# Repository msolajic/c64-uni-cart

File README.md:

# c64-uni-cart
Hardware design of Magic Desk and Ocean compatible cartridge for the Commodore 64

This is the hardware part that accompanies the project of [Magic Desk Cartridge Generator](https://bitbucket.org/zzarko/magic-desk-cartridge-generator/)

This project is free to use and you can use any PCB manufacturer by downloading the Gerber files, but if you would like to support my work and help with further C64 hardware development you can order these PCBs on PCBWay trough this link:

You will get cheap and professionally made PCBs, I will get credits that will help with this and [other projects](https://www.pcbway.com/project/member/?bmbno=1DE407A1-1650-47). Also, if you have to register to that site, [you can use this link](https://pcbway.com/g/YFnBAc) to get bonus initial credit.

Hardware Description
--------------------

Magic Desk cartridges, in their original form, could hold up to 128Kb of code, or up to 16 banks of 8Kb each. Bank selection is done by writing a byte to $DE00. If bit 8 is set, then EXROM is disabled and RAM in the range of $8000 - $9FFF is usable.

This cartridge expands on the idea by having 128 banks of 8Kb available, thus the maximum size is 1 Mb.

Inputs of an 8-bit latch (74LS273) are connected to the data lines. Correct decoding for the I/O1 signal is done by combining PHI2 and I/O1 trough the NOR gates of 74LS02. The only feature that is deviant from the original Magic Desk specification, is that when you disable the cartridge by writing a value of $80 or larger to $DE00, the banking mechanism gets locked and no more write attempts to $DE00 will change the register's state until a hardware reset is performed. This had to be done because some programs would unintentionally write to $DE00 (or any other location in the I/O1 range) and sometimes, if $01 is wrongly set by the program, it could result in a crash. Since the use of this particular cartrige is primarily to enable making onefile program compilations trough the [Magic Desk Cartridge Generator](https://bitbucket.org/zzarko/magic-desk-cartridge-generator/), we have decided to do it this way. If you want (or need) full compatibility with the original Magic Desk cartridge hardware, we have left a jumper to disable this behaviour. Cut the track exposed on the LOCK jumper ("YES" position) on the bottom side of the cartridge PCB, and connect it to the "NO" position. This way the locking mechanism is disabled, but still you can remove the cartridge from the memory map by setting the bit 7 of the latch high.

The PCB was designed to accomodate various types of EPROMs and their FLASH variants. The smallest EPROM you can use is 27C512 (64Kb), and the largest is 27C040 (512 Kb). There is an option to expand the board to a full 1Mb, which will be explained below.

Jumper configuration
--------------------

Do not be intimidated with the amount of jumpers on the board. They are preconfigured for Magic Desk cartridges. I you need Ocean (and other types of cartridges) compatibility, please continue reading, it is described further below. First, you need to configure the memory selection jumpers.

In order to support most common types of EPROMs and FLASH EPROMs, a bank of solder jumpers had to be placed on the bottom side of the PCB. They look like this:

These jumpers HAVE to be configured before plugging the cartridge to your C64! Different types of EPROMs and their FLASH variants have some pins swapped, and if you are using a chip smaller than the maximum size, the unused address lines have to be pulled high on the EPROM side to ensure proper functioning. Also, 27C512 is "shorter" by 4 pins, so it's power supply pin must be connected to +5V instead of being allocated as A17 on the larger ones. The leftmost pins of all 3 jumpers are +5V, and the rightmost pins are the address lines. The middle pins of the jumpers are connected according to the table:

|    Jumper   | Pin | Description                                 |
|-------------|-----|---------------------------------------------|
| PIN1        | 1   | routes either A18 or VCC to pin 1 of EPROM  |
| PIN31       | 31  | routes either A18 or VCC to pin 31 of EPROM |
| 28PIN/32PIN | 30  | routes either A17 or VCC to pin 30 of EPROM |

Here is the table for configuring the jumpers on most common variants of EPROMS and their FLASH counterparts.

| Jumper      |    27C512     |    27C010     |    29F010     |    27C020     |    29F020     |    27C040     |    29F040     |
|-------------|---------------|---------------|---------------|---------------|---------------|---------------|---------------|
| PIN1        | ```[X X X]``` | ```[X=X X]``` | ```[X=X X]``` | ```[X=X X]``` | ```[X=X X]``` | ```[X=X X]``` | ```[X X=X]``` |
| PIN31       | ```[X X X]``` | ```[X=X X]``` | ```[X=X X]``` | ```[X=X X]``` | ```[X=X X]``` | ```[X X=X]``` | ```[X=X X]``` |
| 28PIN/32PIN | ```[X=X X]``` | ```[X X=X]``` | ```[X X=X]``` | ```[X X=X]``` | ```[X X=X]``` | ```[X X=X]``` | ```[X X=X]``` |

Precautions have been taken to ensure the corectness of the table above. Please, check the datasheet of your particular (FLASH) EPROM and configure the jumpers accordingly.

Beyond 512Kb
------------

Full 1Mb is achievable using a 27C080 or 27C801 EPROM. Other types of memory are not supported. On the right top side of the PCB there are two jumpers marked as "1MB Extend". You should **leave out connections on the jumper PIN1 on the bottom side and configure other jumpers as for 27C040**, move the jumper in the "1MB Extend" block from CE to OE and connect the 1MB jumper, as seen in the pictures. Note that this breaks Ocean compatibility.

Advanced Jumper Configuration
-----------------------------

The board has 5 jumpers that are associated with the change of functions from Magic Desk to Ocean (and others). Ocean cartridges are differently mapped in memory, depending on their size. 128k and 512k games use plain 8k /EXROM mapping, but 256k games need to see two different banks in the 16k window.

**MODE** - Completely disable or enable usage of the bit 7 of latch, so Ocean images can work.
- When in position **OCEAN** - bit 7 is disabled, in **MAGIC DESK** - Enabled. 
- Default is **MAGIC DESK**

**LOCK** - Enable or disable latch locking when the latch bit 7 is set (for Ocean, EasyFlash conversions and C64GS). 
- Position **YES** - Enabled, **NO** - Disabled. 
- Default is **YES**. 
- This jumper has no effect if **MODE** is set to **OCEAN** position.
- The effect of this jumper is that you can remove the cartridge temporarily from the memory map by setting bit 7 high, but if needed, it can be re-enabled. 

**GAME** - Enable 16K mapping by pulling /GAME low together with /EXROM ($8000-$9FFF & $A000-$BFFF)
- This is used for EasyFlash conversions and Ocean carts that require two 8k banks. 
- Depending on **SIZE**, this will either show the same 8K bank mirrored in both windows (if **SIZE** is in 8k position) or two different 8k banks (if **SIZE** is set to 16k)

**SIZE** - Map C64 A13 to A18 of the EPROM (for 16K configurations). 
- To be used in conjuction with **GAME** and **MD** jumper.
- If **GAME** jumper is set, and **SIZE** is left at 8k position, both 8k windows show the same data. 
- If **SIZE** is in 16k position, two 8k windows show different data. 

**MD** - If no 16k configuration is needed, leave closed and don't install diodes and resistor on the bottom. If any 16K configuration is needed, cut and install 2x1N4148 diodes and 10k resistor.
- This connects both /ROML and /ROMH to /OE of the EPROM.

Examples for configuring jumpers
--------------------------------

### Ocean 128k
(Batman The Movie, Double Dragon, Navy Seals, Pang etc.)
- Use a 128k EPROM or FLASH, set the memory type selection jumpers accordingly. 
- Set **MODE** jumper to OCEAN.

### Ocean 256K
(Shadow of the Beast, Robocop 2, Chase HQ 2)
- Use a 512k EPROM or FLASH. You need to program the same image in both 256k halves of the EPROM. Set memory type selection jumpers accordingly.
- Use the following jumper settings: **MODE** Ocean, **LOCK** No, **SIZE** 16k, **GAME** connected, **MD** disconnected, resistor and diodes installed.

### Ocean 512k
(Terminator 2)
- Use a 512k EPROM or FLASH, set the memory type selection jumpers accordingly.
- Move **MODE** from MAGIC DESK to OCEAN.

### C64GS / System 3
- Myth and Last Ninja work with the following configuration:
- **MODE** Magic, **LOCK** No, **SIZE** 8k, **GAME** disconnected, **MD** connected, resistor and diodes **NOT** installed.
- Myth reqires you to type **SYS 3 MYTH** on the black screen to start the game.
- C64GS cartridge doesn't work - it writes wrong banks as it uses STA $DE00,X. This would need to be changed to STX $DE00, and one STA $DE00 needs to be changed to LDA #$00, STA $DE00. I'm investigating the possible patch.
- Probably the former is also valid for the recently leaked Elite .crt files. I haven't investigated them yet.

### EasyFlash conversions
Some of EasyFlash games can be converted to use this cartridge. Usually, if the game doesn't use eAPI or is not converted with disk2easyflash, then it can be converted. The startup code (because Easyflash starts in ULTIMAX mode which cannot be emulated here) needs also to be moved, if needed. Here are some games that I successfully converted to use this cartridge:
- [Mayhem in Monsterland](https://csdb.dk/release/?id=127251)
    - Requres a 512Kb chip
    - Export the .crt file using [crt2chip2](https://csdb.dk/release/?id=187607)
    - Using a hex editor, take the first 256Kb of both U4 and U3 files, and concatenate them to one file (First the data from U4, then from U3)
    - Find all banking routines and patch them to use $0x instead of $4x.
    - Patch out any $DE02 access by NOP
    - Use the following jumper settings: **MODE** Magic, **LOCK** No, **SIZE** 16k, **GAME** connected, **MD** disconnected, resistor and diodes installed.
    - Patch file for use with bspatch ([Windows](https://www.pokorra.de/coding/bsdiff.html) / [Linux](http://www.daemonology.net/bsdiff/)) available [HERE](./patch/MayhemInMonsterland.diff)

- [Creatures 2](https://csdb.dk/release/?id=129448)
    - Requres a 512Kb chip
    - Export the .crt file using [crt2chip2](https://csdb.dk/release/?id=187607)
    - Only the U4 file is needed.
    - Minimal startup code and vector initialization needs to be added to the first bank of the cartridge file ($0000 - $2000), part of the code is in U3 file. There is some empty space at $1FE0, use it wisely...
    - CBM80 signature needs to be altered to point to the newly added startup code
    - Use the following jumper settings: **MODE** Magic, **LOCK** No, **SIZE** 8k, **GAME** disconnected, **MD** connected, resistor and diodes **NOT** installed.
    - Patch file for use with bspatch ([Windows](https://www.pokorra.de/coding/bsdiff.html) / [Linux](http://www.daemonology.net/bsdiff/)) available [HERE](./patch/Creatures2.diff)
    
- [Prince of Persia](https://csdb.dk/release/?id=102540)
    - Requres a 512Kb chip
    - Export the .crt file using [crt2chip2](https://csdb.dk/release/?id=187607)
    - Using a hex editor, load the resulting U4 file at offset $00000 and U3 file at offset $40000, and save them as one file.
    - Startup code and vector initialization needs to be patched, as it will be available at $A000 and not at $E000. 
    - CBM80 signature needs to be added to point to the startup code. The BASIC SYS command is at offset $00000, you can patch it out as it turns out it is not used.
    - Use the following jumper settings: **MODE** Magic, **LOCK** No, **SIZE** 16k, **GAME** connected, **MD** disconnected, resistor and diodes installed.
    - Patch file for use with bspatch ([Windows](https://www.pokorra.de/coding/bsdiff.html) / [Linux](http://www.daemonology.net/bsdiff/)) available [HERE](./patch/pop.diff)
    - **NOTE**: The game is not play-tested, as I suck in playing it. Feedback is appreciated. Also, probably the save function (available after level 4) will not work and will crash the machine.
    
As I patch more games, I'll describe the process here. Useful tools for patching are [C64Debugger](https://csdb.dk/release/?id=187948) and [Regenerator](https://csdb.dk/release/?id=149429).

RESET button
------------

The pads for the RESET button will accomodate a vertical miniature tact switch. 

Capacitors
----------

The capacitors are not needed, but you can populate them. They are 100nF 50V MLCC capacitors with 2.54mm raster.

Enclosure compatibility
-----------------------

The PCB is designed so it can be used in various types of cartridge cases. It has been mainly designed to fit the "Stumpy" cartridge from [TFW8B](https://www.thefuturewas8bit.com/c64romcart.html), but it also fits the original Commodore cases and cases from the Polish companies KRADEX / MASZCZYK which are available at some retailers in Europe. It also fits in several 3D-printed cases available at Thingiverse, and there is also one tailor-made for this cartridge, [case for universal C64 512K cartridge by Vokgear](https://www.thingiverse.com/thing:4801176). In revision 5, a hole has been added to support use of [Protoparts](https://www.protoparts.at/product-category/gehaeuse/) enclosures. Unfortunately, I don't have all of the cartridge cases available in the market, so the design is NOT tested to fit with: Individual Computers' and Shareware Plus' (and all other currently available but not mentioned here) cases. 

Please note - the cartridge cases from KRADEX / MASZCZYK are "low profile", and you cannot use a socket for the EPROM with this type of cases!

Also, recently TFW8B came out with their [MARINA 64 cartridge](https://www.thefuturewas8bit.com/shop/commodore/c64/marina64.html). This was not made to compete with their design - actually, development was done concurrently, not knowing what the other party was doing. 

But, where are the EAGLE schematic and PCB design? (Updated!)
-------------------------------------------------------------

~~Glad that you asked. The schematic is available as a .pdf file, and for the time being I'm making only the Gerbers available, because of people taking credit for my designs, removing texts and presenting the cartridges as their own product, thus breaching the license, and later refusing to take action upon notice. I hope that you can understand. You can see from the photos, this was not an easy task to route. If you have good intentions, I will provide you the files via e-mail or other communications channel. The EAGLE files will be made available 6 months from the date of the release (on 1st of October 2020.)~~

EAGLE .sch and .brd files are now available to download in this repository. Please, respect the license when downloading the files.

Revision history
----------------

- Rev.1
    - Initial release, not public
- Rev.2
    - Clearance issue with the diodes and GAME jumper addressed
    - Added 1MB Extension jumpers
    - Enlarged all jumpers
    - Cosmetic improvements
- Rev.3
    - Internal revision, not public
- Rev.4
    - Added place for (optional) 2 LEDs and 2 resistors, for that special bling if you have a transparent case. For best results, use colour changing 3mm LEDs.
    - Table with jumpers on the bottom side is now more legible
    - Added a solder mask stop on the edge connector
- Rev.5
    - Added a smaller hole above the existing one, to enable use of [Protoparts](https://www.protoparts.at/product-category/gehaeuse/) enclosures. Probably now also fits [Individual Computers](http://wiki.icomp.de/wiki/C64_Cartridge_Cases) cases.
    
Thanks:
-------

My thanks go to:

- Žarko Živanov, for creating the Magic Desk Cartridge Generator
- Dan Tootil, for his questions and suggestions that lead to this version of the Cartridge
- TFW8B, for creating such an awesome cartridge case
- Sven Petersen, Edu Arana & Hans Petter Dalsklev, for their knowledge and hardware they are sharing with the community
- Jim Drew, for acknowledging and making this the official CRX2020 Hardware project
- Everyone who ordered any of my PCBs from PCBWay
- and all other people in the Commodore 64 community that I forgot to mention, you guys are awesome!

License
-------
c64-uni-cart is Open Hardware licensed under the [CERN OHL v. 1.2](http://ohwr.org/cernohl), released by Marko Šolajić in 2020. You may redistribute and modify this documentation under the terms of the CERN OHL v.1.2.

A copy of the full license is included in file [LICENSE.txt](LICENSE.txt)

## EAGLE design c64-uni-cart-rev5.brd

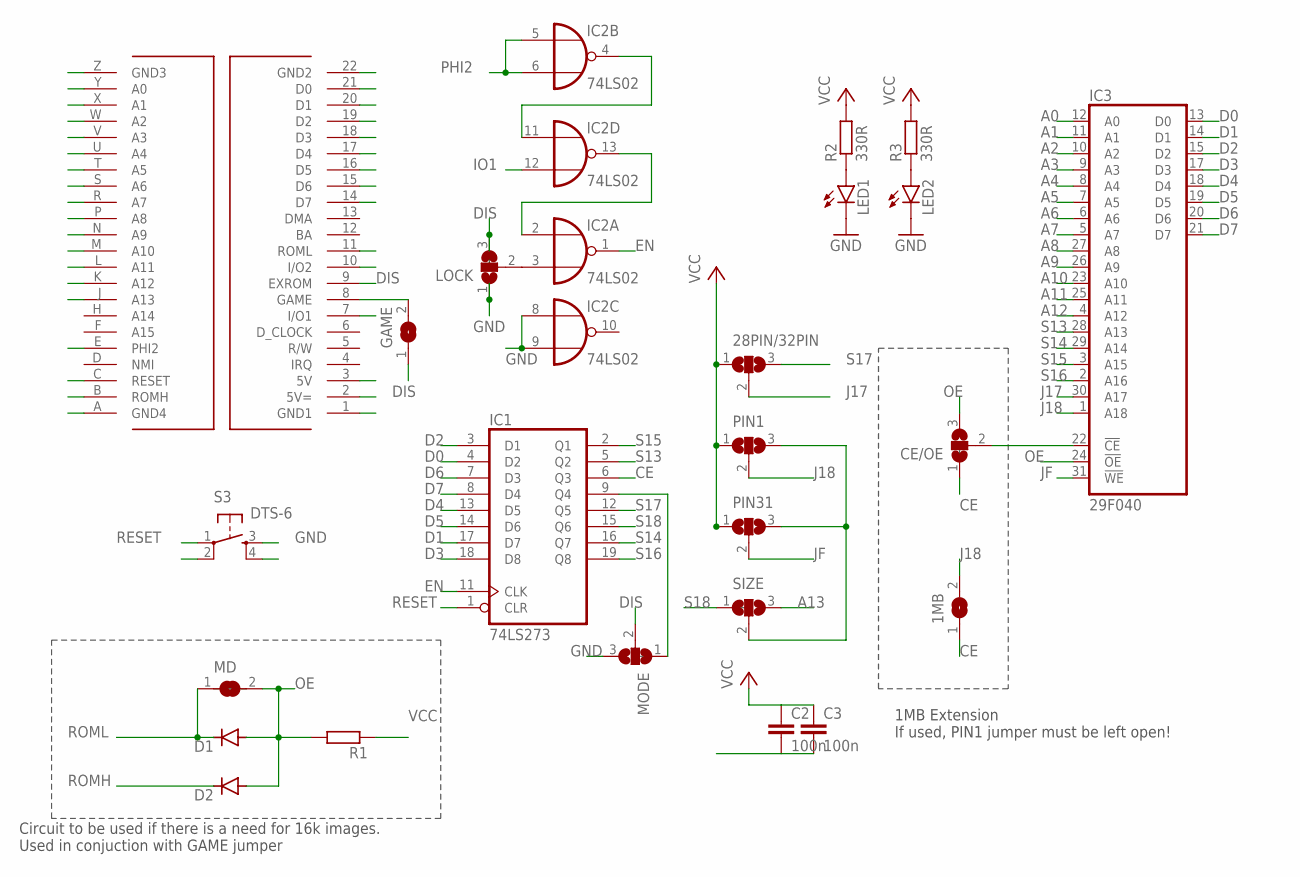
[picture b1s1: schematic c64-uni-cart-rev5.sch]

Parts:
1MB: SJ
28PIN/32PIN: SJ2W; SJ_2
C2, C3: 100n; C025-024X044
CE/OE: SJ2W; SJ_2
D1, D2: DIODE-MINIMELF; MINIMELF
GAME: SJ
IC1: 74LS273; DIL20
IC2: 74LS02; DIL14
IC3: 29F040; DIL32-6
LED1, LED2: LED3MM
LOCK: SJ2W; SJ_2
MD: SJ
MODE: SJ2W; SJ_2
PIN1, PIN31: SJ2W; SJ_2
R1: R-EU_R1206; R1206
R2, R3: 330R; R0805
S3: DTS-6
SIZE: SJ2W; SJ_2
U$1: C64_CARTRIDGESTUMPY; C64_STUMPY

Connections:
A0: IC3.12 (A0), U$1.Y (A0)
A1: IC3.11 (A1), U$1.X (A1)
A2: IC3.10 (A2), U$1.W (A2)
A3: IC3.9 (A3), U$1.V (A3)
A4: IC3.8 (A4), U$1.U (A4)
A5: IC3.7 (A5), U$1.T (A5)
A6: IC3.6 (A6), U$1.S (A6)
A7: IC3.5 (A7), U$1.R (A7)
A8: IC3.27 (A8), U$1.P (A8)
A9: IC3.26 (A9), U$1.N (A9)
A10: IC3.23 (A10), U$1.M (A10)
A11: IC3.25 (A11), U$1.L (A11)
A12: IC3.4 (A12), U$1.K (A12)
A13: SIZE.3, U$1.J (A13)
CE: 1MB.1, CE/OE.1, IC1.6 (Q3)
D0: IC1.4 (D2), IC3.13 (D0), U$1.21 (D0)
D1: IC1.17 (D7), IC3.14 (D1), U$1.20 (D1)
D2: IC1.3 (D1), IC3.15 (D2), U$1.19 (D2)
D3: IC1.18 (D8), IC3.17 (D3), U$1.18 (D3)
D4: IC1.13 (D5), IC3.18 (D4), U$1.17 (D4)
D5: IC1.14 (D6), IC3.19 (D5), U$1.16 (D5)
D6: IC1.7 (D3), IC3.20 (D6), U$1.15 (D6)
D7: IC1.8 (D4), IC3.21 (D7), U$1.14 (D7)
DIS: GAME.1, LOCK.3, MODE.2, U$1.9 (EXROM)
EN: IC1.11 (CLK), IC2.1 (O)
GND: C2.2, C3.2, IC1.10 (GND), IC2.7 (GND), IC2.8 (I0), IC2.9 (I1), IC3.16 (GND), LED1.K (C), LED2.K (C), LOCK.1, MODE.3, S3.3, S3.4, U$1.1 (GND1), U$1.22 (GND2), U$1.A (GND4), U$1.Z (GND3)
IO1: IC2.12 (I1), U$1.7 (I/O1)
IO2: U$1.10 (I/O2)
J17: 28PIN/32PIN.2, IC3.30 (A17)
J18: 1MB.2, IC3.1 (A18), PIN1.2
JF: IC3.31 (!WE), PIN31.2
unnamed: GAME.2, U$1.8 (GAME)
unnamed: IC2.3 (I1), LOCK.2
unnamed: CE/OE.2, IC3.22 (!CE)
unnamed: PIN1.3, PIN31.3, SIZE.2
unnamed: IC1.9 (Q4), MODE.1
unnamed: IC2.4 (O), IC2.11 (I0)
unnamed: IC2.2 (I0), IC2.13 (O)
unnamed: LED1.A, R2.1
unnamed: LED2.A, R3.1
OE: CE/OE.3, D1.A, D2.A, IC3.24 (!OE), MD.2, R1.2
PHI2: IC2.5 (I0), IC2.6 (I1), U$1.E (PHI2)
RESET: IC1.1 (CLR), S3.1, S3.2, U$1.C (RESET)
ROMH: D2.C, U$1.B (ROMH)
ROML: D1.C, MD.1, U$1.11 (ROML)
S13: IC1.5 (Q2), IC3.28 (A13)
S14: IC1.16 (Q7), IC3.29 (A14)
S15: IC1.2 (Q1), IC3.3 (A15)
S16: IC1.19 (Q8), IC3.2 (A16)
S17: 28PIN/32PIN.3, IC1.12 (Q5)
S18: IC1.15 (Q6), SIZE.1
VCC: 28PIN/32PIN.1, C2.1, C3.1, IC1.20 (VCC), IC2.14 (VCC), IC3.32 (VCC), PIN1.1, PIN31.1, R1.1, R2.2, R3.2, U$1.2 (5V=), U$1.3 (5V)

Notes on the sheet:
Circuit to be used if there is a need for 16k images. Used in conjuction with GAME jumper
1MB Extension If used, PIN1 jumper must be left open!

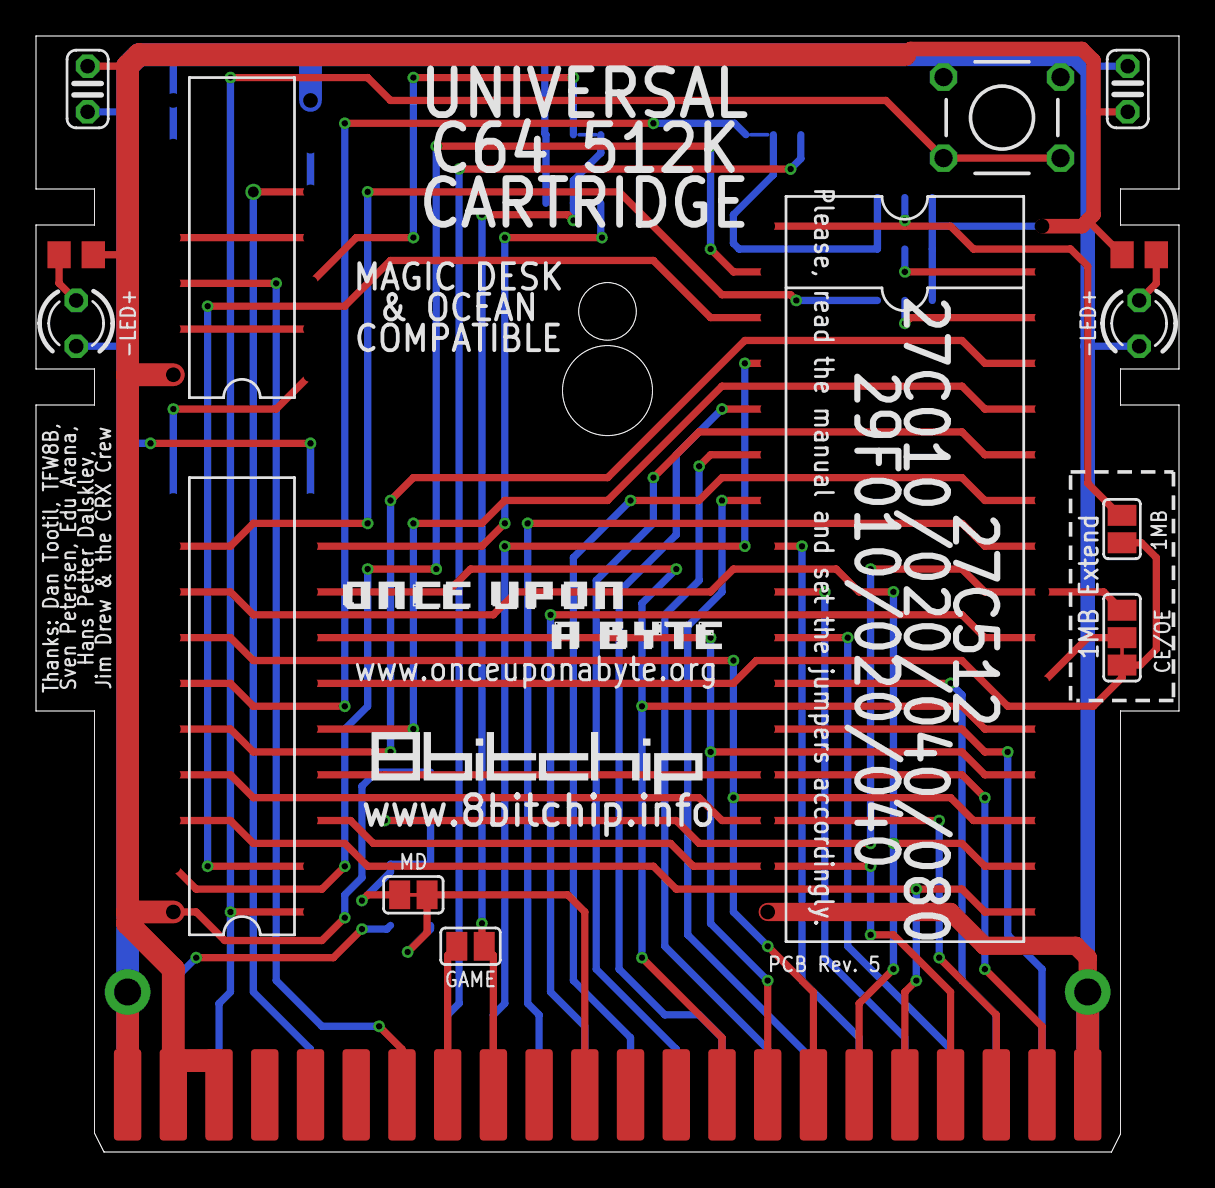
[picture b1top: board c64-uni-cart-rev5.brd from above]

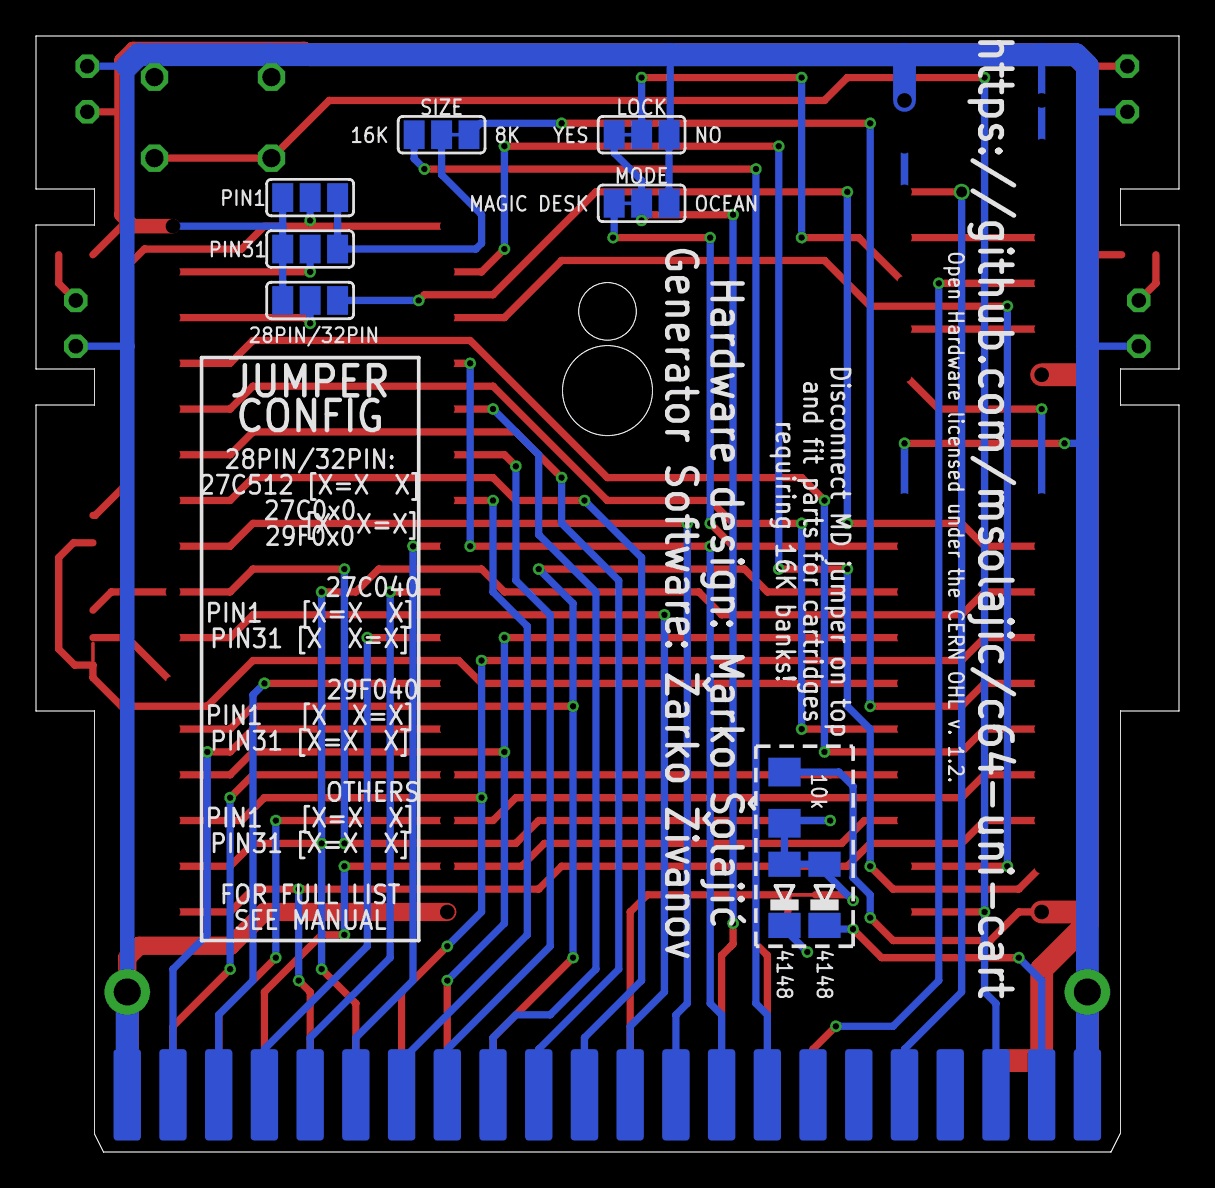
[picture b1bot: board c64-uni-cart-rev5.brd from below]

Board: 2 copper layers, 63.5 x 62.0 mm, 24 parts (9 on the bottom side), 51 nets.

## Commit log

2020-04-25 Add patch for Prince of Persia
2020-04-25 Add patch instructions for Prince of Persia
2020-10-06 Added EAGLE .brd and .sch files
2022-02-10 Rename c64-uni-cart.sch to old/c64-uni-cart.sch
2022-02-10 Rename c64-uni-cart.brd to old/c64-uni-cart.brd
2022-02-10 Revision 4
2023-01-01 Update to revision 5
    PCB Revision 5 adds a second hole, to increase compatibility with different cartridge cases.

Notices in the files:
README.md:
c64-uni-cart is Open Hardware licensed under the [CERN OHL v. 1.2](http://ohwr.org/cernohl), released by Marko Šolajić in 2020. You may redistribute and modify this documentation under the terms of the CERN OHL v.1.2.
A copy of the full license is included in file [LICENSE.txt](LICENSE.txt)
